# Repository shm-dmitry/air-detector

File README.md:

Project info
=======

Project released.

This project contains 2 boards with different sensor sets.

Board#1:
- CO2
- TVOC
- NOx
- Temperature
- Humidity
- PMx (dust)
- H2S (hydrogen sulfide)
- CO (carbon monoxide)
- O2 (oxygen)

Board#2
- TVOC
- NOx
- Temperature
- Humidity
- H2S (hydrogen sulfide)
- Light (in percents, not in Lumens)

It controls:
- Exhaust fan 
- Cooling fan with speed control (fan_pwm driver) 

Additional features:
- Integrates with any smart-house system via MQTT protocol (over WIFI)
- Contains touchpad supports multi-click (single click, double click, tripple click etc)
- Contains RGB led to indicate some internal state you want
- OTA updates - just publish new firmware on your local HTTP server and send URL to it into MQTT topic

3D models
=======
- Board#1 - 3d/box-slepingroom*.stl
- Board#2 - 3d/box-bathroom*.stl

Home assistant files
=======
- Board#1 - hass/board1
- Board#2 - hass/board2

Project status
=======

- Board#1 - Done
- Board#2 - Done

Photos
=======
Board#1:

Board#2:

MQTT Broker data:

Board#1: topic `/air/1`

Board#2: topic `/air/0`

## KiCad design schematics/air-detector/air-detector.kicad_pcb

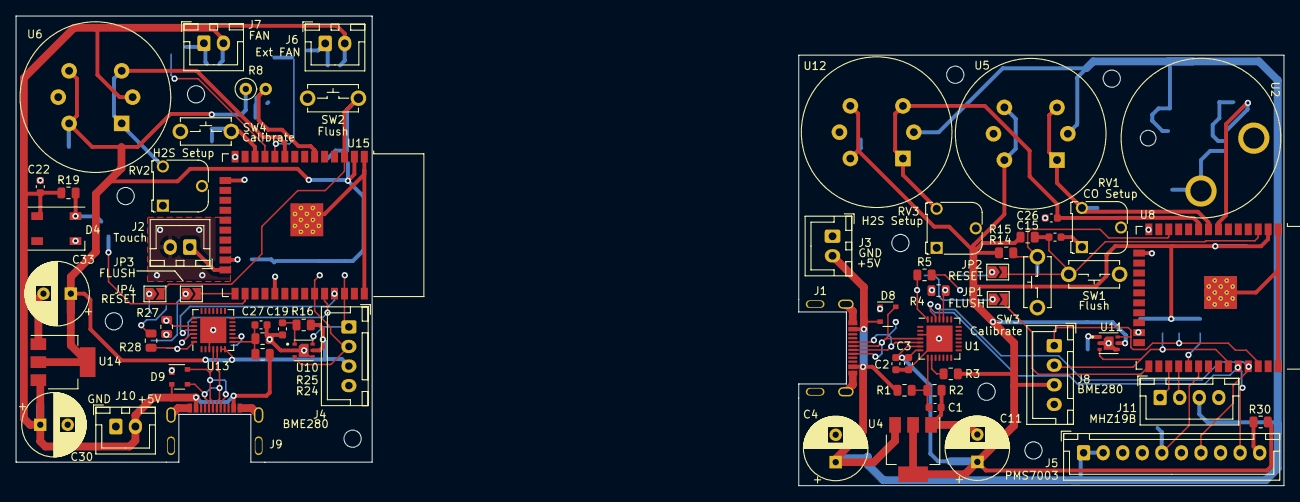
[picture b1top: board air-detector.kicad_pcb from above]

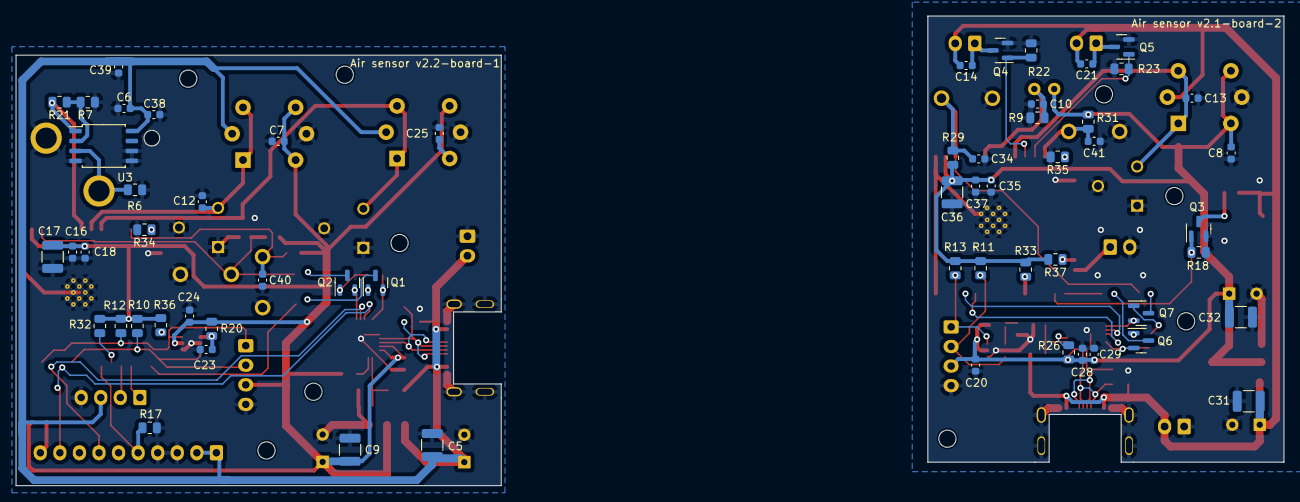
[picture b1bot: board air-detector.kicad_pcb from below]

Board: 2 copper layers, 162.0 x 60.0 mm, 132 parts (59 on the bottom side), 66 nets.

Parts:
C1, C2, C3, C6, C27, C28, C29: 10 uF; C_0603_1608Metric
C4, C11, C30, C33: 1000 uF; CP_Radial_D8.0mm_P3.50mm
C5, C9, C17, C31, C32, C36: 22 uF; C_1210_3225Metric
C7, C8, C10, C12, C14, C15, C19, C20, C21, C23, C24, C25, C34, C39, C40, C41: 1 uF; C_0603_1608Metric
C13, C26: 100 nF; C_0603_1608Metric
C16, C22, C35: 100 uF; C_0603_1608Metric
C18, C37, C38: 0.1 uF; C_0603_1608Metric
D4: SK6812; LED_SK6812_PLCC4_5.0x5.0mm_P3.2mm
D8, D9: PRTR5V0U2X; SOT-143
H1, H2, H3, H4, H5, H6, H7, H8, H9: MountingHole; MountingHole_2.2mm_M2
J1, J9: USB_C_Receptacle_USB2.0; USB_C_P16_MIDMOUNT_1.6
J2: Touch sensor; JST_XH_B2B-XH-A_1x02_P2.50mm_Vertical
J3, J10: 5V input; JST_XH_B2B-XH-A_1x02_P2.50mm_Vertical
J4, J8: BME280; JST_XH_B4B-XH-A_1x04_P2.50mm_Vertical
J5: PMS7003; JST_XH_B10B-XH-A_1x10_P2.50mm_Vertical
J6: Ext FAN; JST_XH_B2B-XH-A_1x02_P2.50mm_Vertical
J7: FAN; JST_XH_B2B-XH-A_1x02_P2.50mm_Vertical
J11: MHZ19B; JST_XH_B4B-XH-A_1x04_P2.50mm_Vertical
JP1, JP3: FLUSH; SolderJumper-2_P1.3mm_Open_TrianglePad1.0x1.5mm
JP2, JP4: RESET; SolderJumper-2_P1.3mm_Open_TrianglePad1.0x1.5mm
Q1, Q2, Q6, Q7: BC847; SOT-23
Q3, Q4, Q5: IRLML0030; SOT-23
R1, R24: 22K; R_0805_2012Metric
R2, R25: 44K; R_0805_2012Metric
R3, R14, R15, R26, R29, R31: 1K; R_0805_2012Metric
R4, R5, R7, R17, R18, R22, R23, R27, R28, R30, R32, R33, R34, R35, R36, R37: 10K; R_0805_2012Metric
R6: 100; R_0805_2012Metric
R8: 100K; R_Axial_DIN0207_L6.3mm_D2.5mm_P2.54mm_Vertical
R9: 100K; R_0805_2012Metric
R10, R11, R12, R13: 3K3; R_0805_2012Metric
R16, R20: 4R7; R_0805_2012Metric
R19: 500; R_0805_2012Metric
R21: 30K; R_0805_2012Metric
RV1: 10K; Potentiometer_Runtron_RM-065_Vertical
RV2, RV3: 20K; Potentiometer_Runtron_RM-065_Vertical
SW1, SW2, SW3, SW4: KLS7-TS3601-5.0-180; SW_PUSH_P6.5_W3.5
U1, U13: CP2102N-Axx-xQFN28; QFN-28-1EP_5x5mm_P0.5mm_EP3.35x3.35mm
U2: O2A2
U3: LM358ADR; SOP-8_5.28x5.23mm_P1.27mm
U4, U14: AMS1117-3.3; SOT-223-3_TabPin2
U5: MQ-7; MQ-6
U6, U12: MQ-136; MQ-6
U8, U15: ESP32-WROOM-32
U10, U11: SGP41; XDCR_SGP41-D-R4

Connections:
/board1/+3V3: C2.1, C3.1, C7.2, C9.2, C11.1, C16.2, C17.2, C18.1, C24.2, C25.2, J8.3, R3.2, R10.1, R12.1, R14.1, R15.1, R20.1, R30.2, R32.2, R36.2, U1.6 (VDD), U1.7 (VREGIN), U4.2 (VO), U5.4 (A2), U5.6 (A1), U8.2 (VDD), U11.5 (VCC_H), U12.4 (A2), U12.6 (A1)
/board1/+5V: C4.1, C5.2, C6.2, C38.2, C39.2, D8.2 (K), J1.A4 (VBUS), J1.A9 (VBUS), J1.B4 (VBUS), J1.B9 (VBUS), J3.2, J5.1, J5.2, J11.3, R1.1, U3.8 (V+), U4.3 (VI), U5.2 (VH+), U12.2 (VH+)
/board1/CO: C12.2, RV1.3, U5.1 (B1), U5.3 (B2), U8.8 (IO32)
/board1/H2S: C26.2, RV3.3, U8.9 (IO33), U12.1 (B1), U12.3 (B2)
/board1/O2: R21.2, U3.1, U8.7 (IO35)
/board1/PMS7003_ENABLE: J5.5, R17.2, U8.30 (IO18)
/board1/RXD_2_3V3: J11.2, U8.28 (IO17)
/board1/RXD_3V3: J5.7, U1.25 (RXD), U8.35 (TXD0/IO1)
/board1/SCL_3V3: J8.1, R12.2, U8.36 (IO22), U11.6 (SCL)
/board1/SDA_3V3: J8.2, R10.2, U8.33 (IO21), U11.3 (SDA)
/board1/TXD_2_3V3: J11.1, U8.27 (IO16)
/board1/TXD_3V3: J5.9, U1.26 (TXD), U8.34 (RXD0/IO3)
/board2/+3V3: C8.2, C20.2, C28.1, C29.1, C32.2, C33.1, C35.2, C36.2, C37.1, J4.3, R8.1, R11.1, R13.1, R16.1, R26.2, R29.1, R31.1, R33.2, R37.2, U6.4 (A2), U6.6 (A1), U10.5 (VCC_H), U13.6 (VDD), U13.7 (VREGIN), U14.2 (VO), U15.2 (VDD)
/board2/+5V: C14.2, C21.2, C22.2, C30.1, C31.2, D4.3 (VDD), D9.2 (K), J6.2, J7.2, J9.A4 (VBUS), J9.A9 (VBUS), J9.B4 (VBUS), J9.B9 (VBUS), J10.2, R19.1, R24.1, U6.2 (VH+), U14.3 (VI)
/board2/EXT_FAN_ENABLE: Q4.1 (G), R22.1, U15.10 (IO25)
/board2/FAN_ENABLE: Q5.1 (G), R23.1, U15.11 (IO26)
/board2/H2S: C13.2, RV2.3, U6.1 (B1), U6.3 (B2), U15.9 (IO33)
/board2/LIGHT: C10.2, R8.2, R9.1, U15.6 (IO34)
/board2/RGB_CONTROL#: Q3.1 (G), R18.1, U15.26 (IO4)
/board2/SCL_3V3: J4.1, R13.2, U10.6 (SCL), U15.36 (IO22)
/board2/SDA_3V3: J4.2, R11.2, U10.3 (SDA), U15.33 (IO21)
/board2/TOUCH_SENSOR: J2.1, U15.24 (IO2)
/core1/CALIBRATE_BUTTON: C41.1, R31.2, SW4.2, U15.12 (IO27)
/core1/D+: D9.4 (K), J9.A6 (D+), J9.B6 (D+), U13.4 (D+)
/core1/D-: D9.3 (K), J9.A7 (D-), J9.B7 (D-), U13.5 (D-)
/core1/ESP32_ENABLE: C34.1, JP4.2 (B), R29.2, SW2.2, U15.3 (EN)
/core1/ESP32_FLUSH: JP3.2 (B), U15.25 (IO0)
/core1/GND: C8.1, C10.1, C13.1, C19.1, C20.1, C22.1, C27.2, C28.2, C29.2, C30.2, C31.1, C32.1, C33.2, C34.2, C35.1, C36.1, C37.2, C41.2, D4.1 (VSS), D9.1 (A), J2.2, J4.4, J9.A1 (GND), J9.A12 (GND), J9.B1 (GND), J9.B12 (GND), J9.S1 (SHIELD), J10.1, Q3.2 (S), Q4.2 (S), Q5.2 (S), R9.2, R18.2, R22.2, R23.2, R25.2, R35.2, RV2.1, RV2.2, SW2.1, SW4.1, U6.5 (VH-), U10.2 (GND1), U10.4 (GND2), U10.7 (PAD), U13.3 (GND), U13.29 (GND), U14.1 (GND), U15.1 (GND), U15.15 (GND), U15.38 (GND), U15.39 (GND)
/core1/RXD_3V3: U13.25 (RXD), U15.35 (TXD0/IO1)
/core1/TXD_3V3: U13.26 (TXD), U15.34 (RXD0/IO3)
/core/CALIBRATE_BUTTON: C40.1, R14.2, SW3.2, U8.12 (IO27)
/core/D+: D8.4 (K), J1.A6 (D+), J1.B6 (D+), U1.4 (D+)
/core/D-: D8.3 (K), J1.A7 (D-), J1.B7 (D-), U1.5 (D-)
/core/ESP32_ENABLE: C15.1, JP2.2 (B), R15.2, SW1.2, U8.3 (EN)
/core/ESP32_FLUSH: JP1.2 (B), U8.25 (IO0)
/core/GND: C1.2, C2.2, C3.2, C4.2, C5.1, C6.1, C7.1, C9.1, C11.2, C12.1, C15.2, C16.1, C17.1, C18.2, C23.1, C24.1, C25.1, C26.1, C38.1, C39.1, C40.2, D8.1 (A), J1.A1 (GND), J1.A12 (GND), J1.B1 (GND), J1.B12 (GND), J1.S1 (SHIELD), J3.1, J5.3, J5.4, J8.4, J11.4, R2.2, R6.2, R7.2, R17.1, R34.2, RV1.1, RV1.2, RV3.1, RV3.2, SW1.1, SW3.1, U1.3 (GND), U1.29 (GND), U2.3 (GND), U3.4 (V-), U3.5 (+), U3.6 (-), U4.1 (GND), U5.5 (VH-), U8.1 (GND), U8.15 (GND), U8.38 (GND), U8.39 (GND), U11.2 (GND1), U11.4 (GND2), U11.7 (PAD), U12.5 (VH-)
unnamed: D4.2 (DIN), Q3.3 (D), R19.2
unnamed: J5.10, R30.1
unnamed: C14.1, J6.1, Q4.3 (D)
unnamed: C21.1, J7.1, Q5.3 (D)
unnamed: JP1.1 (A), Q1.3 (C)
unnamed: JP2.1 (A), Q2.3 (C)
unnamed: JP3.1 (A), Q6.3 (C)
unnamed: JP4.1 (A), Q7.3 (C)
unnamed: Q1.1 (B), R4.2
unnamed: Q1.2 (E), R5.1, U1.28 (~DTR)
unnamed: Q2.1 (B), R5.2
unnamed: Q2.2 (E), R4.1, U1.24 (~RTS)
unnamed: Q6.1 (B), R27.2
unnamed: Q6.2 (E), R28.1, U13.28 (~DTR)
unnamed: Q7.1 (B), R28.2
unnamed: Q7.2 (E), R27.1, U13.24 (~RTS)
unnamed: C1.1, R1.2, R2.1, U1.8 (VBUS)
unnamed: R3.1, U1.9 (~RST)
unnamed: R6.1, U2.2 (OUT), U3.3 (+)
unnamed: R7.1, R21.1, U3.2 (-)
unnamed: R32.1, U8.29 (IO5)
unnamed: R34.1, U8.14 (IO12)
unnamed: R36.1, U8.23 (IO15)
unnamed: C19.2, R16.2, U10.1 (VCC)
unnamed: C23.2, R20.2, U11.1 (VCC)
unnamed: C27.1, R24.2, R25.1, U13.8 (VBUS)
unnamed: R26.1, U13.9 (~RST)
unnamed: R33.1, U15.29 (IO5)
unnamed: R35.1, U15.14 (IO12)
unnamed: R37.1, U15.23 (IO15)

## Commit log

2024-01-15 BME280 integration
2024-01-15 MQTT integration for LED
2024-01-15 touchpad integration
2024-01-15 fan pwm integration
2024-01-16 MQ136 integration
2024-01-16 light sensor integration
2024-01-16 Logging
2024-01-16 fixed problem with ADC during start
2024-01-16 BME280 integration tested
2024-01-17 WIFI enabled, MQTT prefix extracted to separated property
2024-01-17 I2C impl migrated to new API version
2024-01-17 Store MQ156 settings in NVS
2024-01-17 tuning logging in mqtt
2024-01-17 Changed compensation for MQ136
2024-01-17 fixed error while parsing RGBW value for led from MQTT
2024-02-05 Device#1 assembled and ready to install in my appartment
2024-02-05 fixed LED communication timning and default LED data level to reduce 10mA current consumption
2024-02-05 MQ136 - added time/hum adjustment during calibration. Added auto-calibration when several times received negative ppm
2024-02-05 Added home assistant files for board-2
2024-02-06 fix mathematics issue in mq136 - I use 3.3V line offset for measurement, previous formulas was for 5V line offset
2024-02-06 OTA over MQTT & https
2024-02-06 my sdkconfig without my passwords
2024-04-24 1. changes in o2a2 sensor; 2. prepare code for o2a2 sensor
2024-04-24 try to rewrite ADC work to custom framefork to avoid code duplication
2024-04-25 added new drivers
2024-04-25 reduce code size by extracting uart-core common code
2024-04-27 after small test on hardware - added startup delay to O2 sensor; fixed issue in MQTT integration.
2024-04-27 it was bad idea to use N-degree-polynom for approxymation without manual graph recheck. Approxymation formulas changed for MQ7 and MQ136
2024-04-27 fix mistake in formulas
2024-04-29 1. tested MHZ19B integration. 2. Tested BMW280 integration. 3. Fixed mistake in compensation formula in MQ7 integration
2024-04-29 PMS7003 integration tested
2024-05-03 Box printed
2024-05-03 organize logs
2024-05-03 organize import
2024-05-03 added last changes in sdkconfig.example
2024-05-03 new version
2024-05-03 1. added sdkconfig for board#1; added hass files for board1
2024-05-07 fixes in calibration algorithm
2024-05-07 fix infinite restart loop after user requested reboot over healthcheck
2024-05-12 changes in calibration process for ADC-based sensors
2024-05-13 feature - read current settings without
